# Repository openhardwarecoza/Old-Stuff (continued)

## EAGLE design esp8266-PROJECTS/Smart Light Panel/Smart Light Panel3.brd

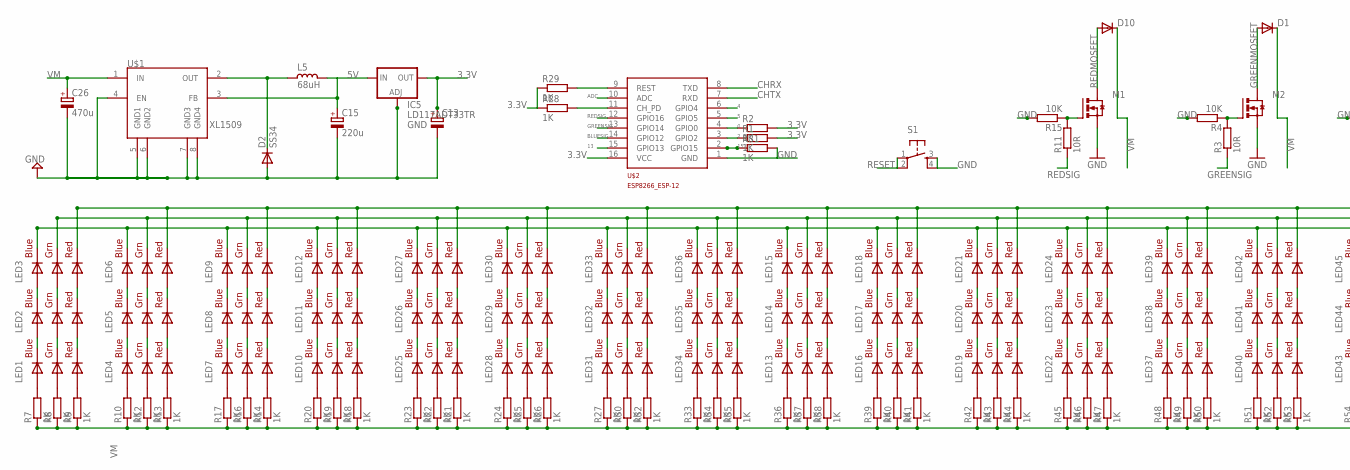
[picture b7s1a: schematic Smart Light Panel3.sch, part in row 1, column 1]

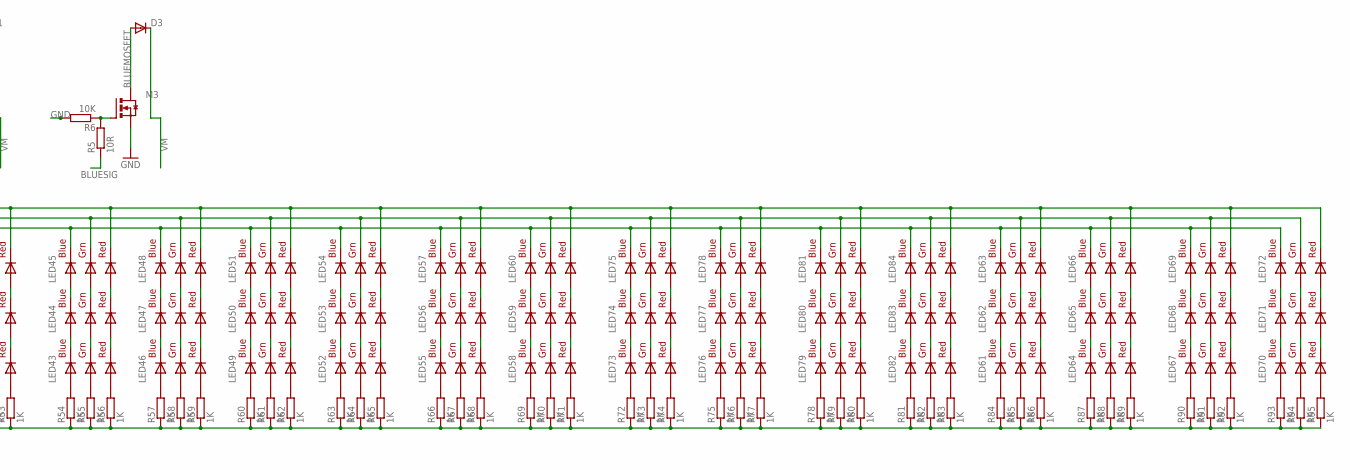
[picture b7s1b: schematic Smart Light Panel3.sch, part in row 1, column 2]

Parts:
C13: CPOL-EUE2.5-7; E2,5-7
C15: 220u; E2,5-7
C26: 470u; E2,5-7
D1, D3, D10: DIODESMA-ALT; SMA-DIODE_ALT
D2: SS34; DO-214AC
IC5: LD117ADT33TR; DPACK
L5: 68uH; CD75
LED1, LED2, LED3, LED4, LED5, LED6, LED7, LED8, LED9, LED10, LED11, LED12, LED13, LED14, LED15, LED16, LED17, LED18, LED19, LED20, LED21, LED22, LED23, LED24, LED25, LED26, LED27, LED28, LED29, LED30, LED31, LED32, LED33, LED34, LED35, LED36, LED37, LED38, LED39, LED40, LED41, LED42, LED43, LED44, LED45, LED46, LED47, LED48, LED49, LED50, LED51, LED52, LED53, LED54, LED55, LED56, LED57, LED58, LED59, LED60, LED61, LED62, LED63, LED64, LED65, LED66, LED67, LED68, LED69, LED70, LED71, LED72, LED73, LED74, LED75, LED76, LED77, LED78, LED79, LED80, LED81, LED82, LED83, LED84: RGBLED5050
M1, M2, M3: IRLR024N; TO252
R1, R2, R28, R29, R31: 1K; M1206
R3, R5, R11: 10R; M1206
R4, R6, R15: 10K; M1206
R7, R8, R9, R10, R12, R13, R14, R16, R17, R18, R19, R20, R21, R22, R23, R24, R25, R26, R27, R30, R32, R33, R34, R35, R36, R37, R38, R39, R40, R41, R42, R43, R44, R45, R46, R47, R48, R49, R50, R51, R52, R53, R54, R55, R56, R57, R58, R59, R60, R61, R62, R63, R64, R65, R66, R67, R68, R69, R70, R71, R72, R73, R74, R75, R76, R77, R78, R79, R80, R81, R82, R83, R84, R85, R86, R87, R88, R89, R90, R91, R92, R93, R94, R95: 1K; R0603
S1: TAC_SWITCHPTH; TACTILE-PTH
U$1: XL1509; SO08
U$2: ESP8266_ESP-12; ESP8266-ESP12

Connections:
0: R2.1, U$2.4 (GPIO0)
2: R1.1, U$2.3 (GPIO2)
3.3V: C13.+, IC5.4 (OUT), R1.2, R2.2, R28.1, R29.1, U$2.16 (VCC)
4: U$2.6 (GPIO4)
5: U$2.5 (GPIO5)
5V: C15.+, IC5.3 (IN), L5.1, U$1.3 (FB)
13: U$2.15 (GPIO13)
15: R31.1, U$2.2 (GPIO15)
ADC: U$2.10 (ADC)
BLUEMOSFET: D3.A, LED3.4 (BLUE_C), LED6.4 (BLUE_C), LED9.4 (BLUE_C), LED12.4 (BLUE_C), LED15.4 (BLUE_C), LED18.4 (BLUE_C), LED21.4 (BLUE_C), LED24.4 (BLUE_C), LED27.4 (BLUE_C), LED30.4 (BLUE_C), LED33.4 (BLUE_C), LED36.4 (BLUE_C), LED39.4 (BLUE_C), LED42.4 (BLUE_C), LED45.4 (BLUE_C), LED48.4 (BLUE_C), LED51.4 (BLUE_C), LED54.4 (BLUE_C), LED57.4 (BLUE_C), LED60.4 (BLUE_C), LED63.4 (BLUE_C), LED66.4 (BLUE_C), LED69.4 (BLUE_C), LED72.4 (BLUE_C), LED75.4 (BLUE_C), LED78.4 (BLUE_C), LED81.4 (BLUE_C), LED84.4 (BLUE_C), M3.3 (D)
BLUESIG: R5.1, U$2.14 (GPIO12)
CHRX: U$2.8 (TXD)
CHTX: U$2.7 (RXD)
GND: C13.-, C15.-, C26.-, D2.2 (A), IC5.1 (ADJ), M1.2 (S), M2.2 (S), M3.2 (S), R4.2, R6.2, R15.2, R31.2, S1.3, S1.4, U$1.4 (EN), U$1.5 (GND1), U$1.6 (GND2), U$1.7 (GND3), U$1.8 (GND4), U$2.1 (GND)
GREENMOSFET: D1.A, LED3.6 (GREEN_C), LED6.6 (GREEN_C), LED9.6 (GREEN_C), LED12.6 (GREEN_C), LED15.6 (GREEN_C), LED18.6 (GREEN_C), LED21.6 (GREEN_C), LED24.6 (GREEN_C), LED27.6 (GREEN_C), LED30.6 (GREEN_C), LED33.6 (GREEN_C), LED36.6 (GREEN_C), LED39.6 (GREEN_C), LED42.6 (GREEN_C), LED45.6 (GREEN_C), LED48.6 (GREEN_C), LED51.6 (GREEN_C), LED54.6 (GREEN_C), LED57.6 (GREEN_C), LED60.6 (GREEN_C), LED63.6 (GREEN_C), LED66.6 (GREEN_C), LED69.6 (GREEN_C), LED72.6 (GREEN_C), LED75.6 (GREEN_C), LED78.6 (GREEN_C), LED81.6 (GREEN_C), LED84.6 (GREEN_C), M2.3 (D)
GREENSIG: R3.1, U$2.13 (GPIO14)
unnamed: M2.1 (G), R3.2, R4.1
unnamed: LED2.4 (BLUE_C), LED3.3 (BLUE_A)
unnamed: LED2.6 (GREEN_C), LED3.1 (GREEN_A)
unnamed: M3.1 (G), R5.2, R6.1
unnamed: LED59.4 (BLUE_C), LED60.3 (BLUE_A)
unnamed: LED2.5 (RED_C), LED3.2 (RED_A)
unnamed: LED1.5 (RED_C), LED2.2 (RED_A)
unnamed: LED59.6 (GREEN_C), LED60.1 (GREEN_A)
unnamed: LED59.5 (RED_C), LED60.2 (RED_A)
unnamed: LED1.6 (GREEN_C), LED2.1 (GREEN_A)
unnamed: LED1.4 (BLUE_C), LED2.3 (BLUE_A)
unnamed: LED4.4 (BLUE_C), LED5.3 (BLUE_A)
unnamed: LED4.6 (GREEN_C), LED5.1 (GREEN_A)
unnamed: LED5.4 (BLUE_C), LED6.3 (BLUE_A)
unnamed: R28.2, U$2.11 (CH_PD)
unnamed: LED5.6 (GREEN_C), LED6.1 (GREEN_A)
unnamed: LED4.5 (RED_C), LED5.2 (RED_A)
unnamed: LED5.5 (RED_C), LED6.2 (RED_A)
unnamed: LED7.4 (BLUE_C), LED8.3 (BLUE_A)
unnamed: LED8.4 (BLUE_C), LED9.3 (BLUE_A)
unnamed: LED7.6 (GREEN_C), LED8.1 (GREEN_A)
unnamed: LED8.6 (GREEN_C), LED9.1 (GREEN_A)
unnamed: LED7.5 (RED_C), LED8.2 (RED_A)
unnamed: LED8.5 (RED_C), LED9.2 (RED_A)
unnamed: LED10.4 (BLUE_C), LED11.3 (BLUE_A)
unnamed: LED11.4 (BLUE_C), LED12.3 (BLUE_A)
unnamed: LED10.6 (GREEN_C), LED11.1 (GREEN_A)
unnamed: LED11.6 (GREEN_C), LED12.1 (GREEN_A)
unnamed: LED10.5 (RED_C), LED11.2 (RED_A)
unnamed: LED11.5 (RED_C), LED12.2 (RED_A)
unnamed: LED25.4 (BLUE_C), LED26.3 (BLUE_A)
unnamed: LED26.4 (BLUE_C), LED27.3 (BLUE_A)
unnamed: LED25.6 (GREEN_C), LED26.1 (GREEN_A)
unnamed: LED26.6 (GREEN_C), LED27.1 (GREEN_A)
unnamed: LED25.5 (RED_C), LED26.2 (RED_A)
unnamed: LED26.5 (RED_C), LED27.2 (RED_A)
unnamed: LED28.4 (BLUE_C), LED29.3 (BLUE_A)
unnamed: LED28.6 (GREEN_C), LED29.1 (GREEN_A)
unnamed: LED29.4 (BLUE_C), LED30.3 (BLUE_A)
unnamed: LED29.6 (GREEN_C), LED30.1 (GREEN_A)
unnamed: LED28.5 (RED_C), LED29.2 (RED_A)
unnamed: LED29.5 (RED_C), LED30.2 (RED_A)
unnamed: LED31.4 (BLUE_C), LED32.3 (BLUE_A)
unnamed: LED32.4 (BLUE_C), LED33.3 (BLUE_A)
unnamed: LED31.6 (GREEN_C), LED32.1 (GREEN_A)
unnamed: LED32.6 (GREEN_C), LED33.1 (GREEN_A)
unnamed: LED31.5 (RED_C), LED32.2 (RED_A)
unnamed: LED32.5 (RED_C), LED33.2 (RED_A)
unnamed: LED34.4 (BLUE_C), LED35.3 (BLUE_A)
unnamed: LED35.4 (BLUE_C), LED36.3 (BLUE_A)
unnamed: LED34.6 (GREEN_C), LED35.1 (GREEN_A)
unnamed: LED35.6 (GREEN_C), LED36.1 (GREEN_A)
unnamed: LED34.5 (RED_C), LED35.2 (RED_A)
unnamed: LED35.5 (RED_C), LED36.2 (RED_A)
unnamed: LED13.4 (BLUE_C), LED14.3 (BLUE_A)
unnamed: LED13.6 (GREEN_C), LED14.1 (GREEN_A)
unnamed: LED13.5 (RED_C), LED14.2 (RED_A)
unnamed: LED14.5 (RED_C), LED15.2 (RED_A)
unnamed: LED14.6 (GREEN_C), LED15.1 (GREEN_A)
unnamed: LED14.4 (BLUE_C), LED15.3 (BLUE_A)
unnamed: LED16.4 (BLUE_C), LED17.3 (BLUE_A)
unnamed: LED16.6 (GREEN_C), LED17.1 (GREEN_A)
unnamed: LED16.5 (RED_C), LED17.2 (RED_A)
unnamed: M1.1 (G), R11.2, R15.1
unnamed: LED17.5 (RED_C), LED18.2 (RED_A)
unnamed: LED17.6 (GREEN_C), LED18.1 (GREEN_A)
unnamed: LED17.4 (BLUE_C), LED18.3 (BLUE_A)
unnamed: LED19.4 (BLUE_C), LED20.3 (BLUE_A)
unnamed: LED19.6 (GREEN_C), LED20.1 (GREEN_A)
unnamed: LED19.5 (RED_C), LED20.2 (RED_A)
unnamed: LED20.5 (RED_C), LED21.2 (RED_A)
unnamed: LED20.6 (GREEN_C), LED21.1 (GREEN_A)
unnamed: LED20.4 (BLUE_C), LED21.3 (BLUE_A)
unnamed: LED22.4 (BLUE_C), LED23.3 (BLUE_A)
unnamed: LED22.6 (GREEN_C), LED23.1 (GREEN_A)
unnamed: LED22.5 (RED_C), LED23.2 (RED_A)
unnamed: LED23.5 (RED_C), LED24.2 (RED_A)
unnamed: LED23.6 (GREEN_C), LED24.1 (GREEN_A)
unnamed: LED23.4 (BLUE_C), LED24.3 (BLUE_A)
unnamed: LED37.4 (BLUE_C), LED38.3 (BLUE_A)
unnamed: LED37.6 (GREEN_C), LED38.1 (GREEN_A)
unnamed: LED37.5 (RED_C), LED38.2 (RED_A)
unnamed: LED38.5 (RED_C), LED39.2 (RED_A)
unnamed: LED38.6 (GREEN_C), LED39.1 (GREEN_A)
unnamed: LED38.4 (BLUE_C), LED39.3 (BLUE_A)
unnamed: LED40.5 (RED_C), LED41.2 (RED_A)
unnamed: LED40.6 (GREEN_C), LED41.1 (GREEN_A)
unnamed: LED40.4 (BLUE_C), LED41.3 (BLUE_A)
unnamed: D2.1 (C), L5.2, U$1.2 (OUT)
unnamed: LED41.4 (BLUE_C), LED42.3 (BLUE_A)
unnamed: LED41.6 (GREEN_C), LED42.1 (GREEN_A)
unnamed: LED41.5 (RED_C), LED42.2 (RED_A)
unnamed: LED43.4 (BLUE_C), LED44.3 (BLUE_A)
unnamed: LED43.6 (GREEN_C), LED44.1 (GREEN_A)
unnamed: LED43.5 (RED_C), LED44.2 (RED_A)
unnamed: LED44.5 (RED_C), LED45.2 (RED_A)
unnamed: LED44.6 (GREEN_C), LED45.1 (GREEN_A)
unnamed: LED44.4 (BLUE_C), LED45.3 (BLUE_A)
unnamed: LED46.4 (BLUE_C), LED47.3 (BLUE_A)
unnamed: LED46.6 (GREEN_C), LED47.1 (GREEN_A)
unnamed: LED46.5 (RED_C), LED47.2 (RED_A)
unnamed: LED47.5 (RED_C), LED48.2 (RED_A)
unnamed: LED47.6 (GREEN_C), LED48.1 (GREEN_A)
unnamed: LED47.4 (BLUE_C), LED48.3 (BLUE_A)
unnamed: LED50.5 (RED_C), LED51.2 (RED_A)
unnamed: LED50.6 (GREEN_C), LED51.1 (GREEN_A)
unnamed: LED50.4 (BLUE_C), LED51.3 (BLUE_A)
unnamed: LED49.4 (BLUE_C), LED50.3 (BLUE_A)
unnamed: LED49.6 (GREEN_C), LED50.1 (GREEN_A)
unnamed: LED49.5 (RED_C), LED50.2 (RED_A)
unnamed: LED52.4 (BLUE_C), LED53.3 (BLUE_A)
unnamed: LED52.6 (GREEN_C), LED53.1 (GREEN_A)
unnamed: LED52.5 (RED_C), LED53.2 (RED_A)
unnamed: LED53.5 (RED_C), LED54.2 (RED_A)
unnamed: LED53.6 (GREEN_C), LED54.1 (GREEN_A)
unnamed: LED53.4 (BLUE_C), LED54.3 (BLUE_A)
unnamed: LED56.5 (RED_C), LED57.2 (RED_A)
unnamed: LED56.6 (GREEN_C), LED57.1 (GREEN_A)
unnamed: LED56.4 (BLUE_C), LED57.3 (BLUE_A)
unnamed: LED55.4 (BLUE_C), LED56.3 (BLUE_A)
unnamed: LED55.6 (GREEN_C), LED56.1 (GREEN_A)
unnamed: LED55.5 (RED_C), LED56.2 (RED_A)
unnamed: LED58.4 (BLUE_C), LED59.3 (BLUE_A)
unnamed: LED58.6 (GREEN_C), LED59.1 (GREEN_A)
unnamed: LED58.5 (RED_C), LED59.2 (RED_A)
unnamed: LED73.4 (BLUE_C), LED74.3 (BLUE_A)
unnamed: LED73.6 (GREEN_C), LED74.1 (GREEN_A)
unnamed: LED73.5 (RED_C), LED74.2 (RED_A)
unnamed: LED74.5 (RED_C), LED75.2 (RED_A)
unnamed: LED74.6 (GREEN_C), LED75.1 (GREEN_A)
unnamed: LED74.4 (BLUE_C), LED75.3 (BLUE_A)
unnamed: LED76.4 (BLUE_C), LED77.3 (BLUE_A)
unnamed: LED77.4 (BLUE_C), LED78.3 (BLUE_A)
unnamed: LED77.6 (GREEN_C), LED78.1 (GREEN_A)
unnamed: LED76.6 (GREEN_C), LED77.1 (GREEN_A)
unnamed: LED76.5 (RED_C), LED77.2 (RED_A)
unnamed: LED77.5 (RED_C), LED78.2 (RED_A)
unnamed: LED80.4 (BLUE_C), LED81.3 (BLUE_A)
unnamed: LED80.6 (GREEN_C), LED81.1 (GREEN_A)
unnamed: LED80.5 (RED_C), LED81.2 (RED_A)
unnamed: LED79.5 (RED_C), LED80.2 (RED_A)
unnamed: LED79.6 (GREEN_C), LED80.1 (GREEN_A)
unnamed: LED79.4 (BLUE_C), LED80.3 (BLUE_A)
unnamed: LED82.4 (BLUE_C), LED83.3 (BLUE_A)
unnamed: LED83.4 (BLUE_C), LED84.3 (BLUE_A)
unnamed: LED83.6 (GREEN_C), LED84.1 (GREEN_A)
unnamed: LED82.6 (GREEN_C), LED83.1 (GREEN_A)
unnamed: LED82.5 (RED_C), LED83.2 (RED_A)
unnamed: LED83.5 (RED_C), LED84.2 (RED_A)
unnamed: LED62.4 (BLUE_C), LED63.3 (BLUE_A)
unnamed: LED61.4 (BLUE_C), LED62.3 (BLUE_A)
unnamed: LED61.6 (GREEN_C), LED62.1 (GREEN_A)
unnamed: LED62.6 (GREEN_C), LED63.1 (GREEN_A)
unnamed: LED62.5 (RED_C), LED63.2 (RED_A)
unnamed: LED61.5 (RED_C), LED62.2 (RED_A)
unnamed: LED65.4 (BLUE_C), LED66.3 (BLUE_A)
unnamed: LED64.4 (BLUE_C), LED65.3 (BLUE_A)
unnamed: LED65.6 (GREEN_C), LED66.1 (GREEN_A)
unnamed: LED64.6 (GREEN_C), LED65.1 (GREEN_A)
unnamed: LED64.5 (RED_C), LED65.2 (RED_A)
unnamed: LED65.5 (RED_C), LED66.2 (RED_A)
unnamed: LED67.4 (BLUE_C), LED68.3 (BLUE_A)
unnamed: LED68.4 (BLUE_C), LED69.3 (BLUE_A)
unnamed: LED68.6 (GREEN_C), LED69.1 (GREEN_A)
unnamed: LED67.6 (GREEN_C), LED68.1 (GREEN_A)
unnamed: LED67.5 (RED_C), LED68.2 (RED_A)
unnamed: LED68.5 (RED_C), LED69.2 (RED_A)
unnamed: LED71.4 (BLUE_C), LED72.3 (BLUE_A)
unnamed: LED70.4 (BLUE_C), LED71.3 (BLUE_A)
unnamed: LED70.6 (GREEN_C), LED71.1 (GREEN_A)
unnamed: LED70.5 (RED_C), LED71.2 (RED_A)
unnamed: LED71.5 (RED_C), LED72.2 (RED_A)
unnamed: LED71.6 (GREEN_C), LED72.1 (GREEN_A)
unnamed: LED1.3 (BLUE_A), R7.2
unnamed: LED1.1 (GREEN_A), R8.2
unnamed: LED1.2 (RED_A), R9.2
unnamed: LED4.3 (BLUE_A), R10.2
unnamed: LED4.1 (GREEN_A), R12.2
unnamed: LED4.2 (RED_A), R13.2
unnamed: LED7.2 (RED_A), R14.2
unnamed: LED7.1 (GREEN_A), R16.2
unnamed: LED7.3 (BLUE_A), R17.2
unnamed: LED10.2 (RED_A), R18.2
unnamed: LED10.1 (GREEN_A), R19.2
unnamed: LED10.3 (BLUE_A), R20.2
unnamed: LED25.2 (RED_A), R21.2
unnamed: LED25.1 (GREEN_A), R22.2
unnamed: LED25.3 (BLUE_A), R23.2
unnamed: LED28.3 (BLUE_A), R24.2
unnamed: LED28.1 (GREEN_A), R25.2
unnamed: LED28.2 (RED_A), R26.2
unnamed: LED31.3 (BLUE_A), R27.2
unnamed: LED31.1 (GREEN_A), R30.2
unnamed: LED31.2 (RED_A), R32.2
unnamed: LED34.3 (BLUE_A), R33.2
unnamed: LED34.1 (GREEN_A), R34.2
unnamed: LED34.2 (RED_A), R35.2
unnamed: LED13.3 (BLUE_A), R36.2
unnamed: LED13.1 (GREEN_A), R37.2
unnamed: LED13.2 (RED_A), R38.2
unnamed: LED16.3 (BLUE_A), R39.2
unnamed: LED16.1 (GREEN_A), R40.2
unnamed: LED16.2 (RED_A), R41.2
unnamed: LED19.3 (BLUE_A), R42.2
unnamed: LED19.1 (GREEN_A), R43.2
unnamed: LED19.2 (RED_A), R44.2
unnamed: LED22.3 (BLUE_A), R45.2
unnamed: LED22.1 (GREEN_A), R46.2
unnamed: LED22.2 (RED_A), R47.2
unnamed: LED37.3 (BLUE_A), R48.2
unnamed: LED37.1 (GREEN_A), R49.2
unnamed: LED37.2 (RED_A), R50.2
unnamed: LED40.3 (BLUE_A), R51.2
unnamed: LED40.1 (GREEN_A), R52.2
unnamed: LED40.2 (RED_A), R53.2
unnamed: LED43.3 (BLUE_A), R54.2
unnamed: LED43.1 (GREEN_A), R55.2
unnamed: LED43.2 (RED_A), R56.2
unnamed: LED46.3 (BLUE_A), R57.2
unnamed: LED46.1 (GREEN_A), R58.2
unnamed: LED46.2 (RED_A), R59.2
unnamed: LED49.3 (BLUE_A), R60.2
unnamed: LED49.1 (GREEN_A), R61.2
unnamed: LED49.2 (RED_A), R62.2
unnamed: LED52.3 (BLUE_A), R63.2
unnamed: LED52.1 (GREEN_A), R64.2
unnamed: LED52.2 (RED_A), R65.2
unnamed: LED55.3 (BLUE_A), R66.2
unnamed: LED55.1 (GREEN_A), R67.2
unnamed: LED55.2 (RED_A), R68.2
unnamed: LED58.3 (BLUE_A), R69.2
unnamed: LED58.1 (GREEN_A), R70.2
unnamed: LED58.2 (RED_A), R71.2
unnamed: LED73.3 (BLUE_A), R72.2
unnamed: LED73.1 (GREEN_A), R73.2
unnamed: LED73.2 (RED_A), R74.2
unnamed: LED76.3 (BLUE_A), R75.2
unnamed: LED76.1 (GREEN_A), R76.2
unnamed: LED76.2 (RED_A), R77.2
unnamed: LED79.3 (BLUE_A), R78.2
unnamed: LED79.1 (GREEN_A), R79.2
unnamed: LED79.2 (RED_A), R80.2
unnamed: LED82.3 (BLUE_A), R81.2
unnamed: LED82.1 (GREEN_A), R82.2
unnamed: LED82.2 (RED_A), R83.2
unnamed: LED61.3 (BLUE_A), R84.2
unnamed: LED61.1 (GREEN_A), R85.2
unnamed: LED61.2 (RED_A), R86.2
unnamed: LED64.3 (BLUE_A), R87.2
unnamed: LED64.1 (GREEN_A), R88.2
unnamed: LED64.2 (RED_A), R89.2
unnamed: LED67.3 (BLUE_A), R90.2
unnamed: LED67.1 (GREEN_A), R91.2
unnamed: LED67.2 (RED_A), R92.2
unnamed: LED70.3 (BLUE_A), R93.2
unnamed: LED70.1 (GREEN_A), R94.2
unnamed: LED70.2 (RED_A), R95.2
REDMOSFET: D10.A, LED3.5 (RED_C), LED6.5 (RED_C), LED9.5 (RED_C), LED12.5 (RED_C), LED15.5 (RED_C), LED18.5 (RED_C), LED21.5 (RED_C), LED24.5 (RED_C), LED27.5 (RED_C), LED30.5 (RED_C), LED33.5 (RED_C), LED36.5 (RED_C), LED39.5 (RED_C), LED42.5 (RED_C), LED45.5 (RED_C), LED48.5 (RED_C), LED51.5 (RED_C), LED54.5 (RED_C), LED57.5 (RED_C), LED60.5 (RED_C), LED63.5 (RED_C), LED66.5 (RED_C), LED69.5 (RED_C), LED72.5 (RED_C), LED75.5 (RED_C), LED78.5 (RED_C), LED81.5 (RED_C), LED84.5 (RED_C), M1.3 (D)
REDSIG: R11.1, U$2.12 (GPIO16)
RESET: R29.2, S1.1, S1.2, U$2.9 (REST)
VM: C26.+, D1.C, D3.C, D10.C, R7.1, R8.1, R9.1, R10.1, R12.1, R13.1, R14.1, R16.1, R17.1, R18.1, R19.1, R20.1, R21.1, R22.1, R23.1, R24.1, R25.1, R26.1, R27.1, R30.1, R32.1, R33.1, R34.1, R35.1, R36.1, R37.1, R38.1, R39.1, R40.1, R41.1, R42.1, R43.1, R44.1, R45.1, R46.1, R47.1, R48.1, R49.1, R50.1, R51.1, R52.1, R53.1, R54.1, R55.1, R56.1, R57.1, R58.1, R59.1, R60.1, R61.1, R62.1, R63.1, R64.1, R65.1, R66.1, R67.1, R68.1, R69.1, R70.1, R71.1, R72.1, R73.1, R74.1, R75.1, R76.1, R77.1, R78.1, R79.1, R80.1, R81.1, R82.1, R83.1, R84.1, R85.1, R86.1, R87.1, R88.1, R89.1, R90.1, R91.1, R92.1, R93.1, R94.1, R95.1, U$1.1 (IN)

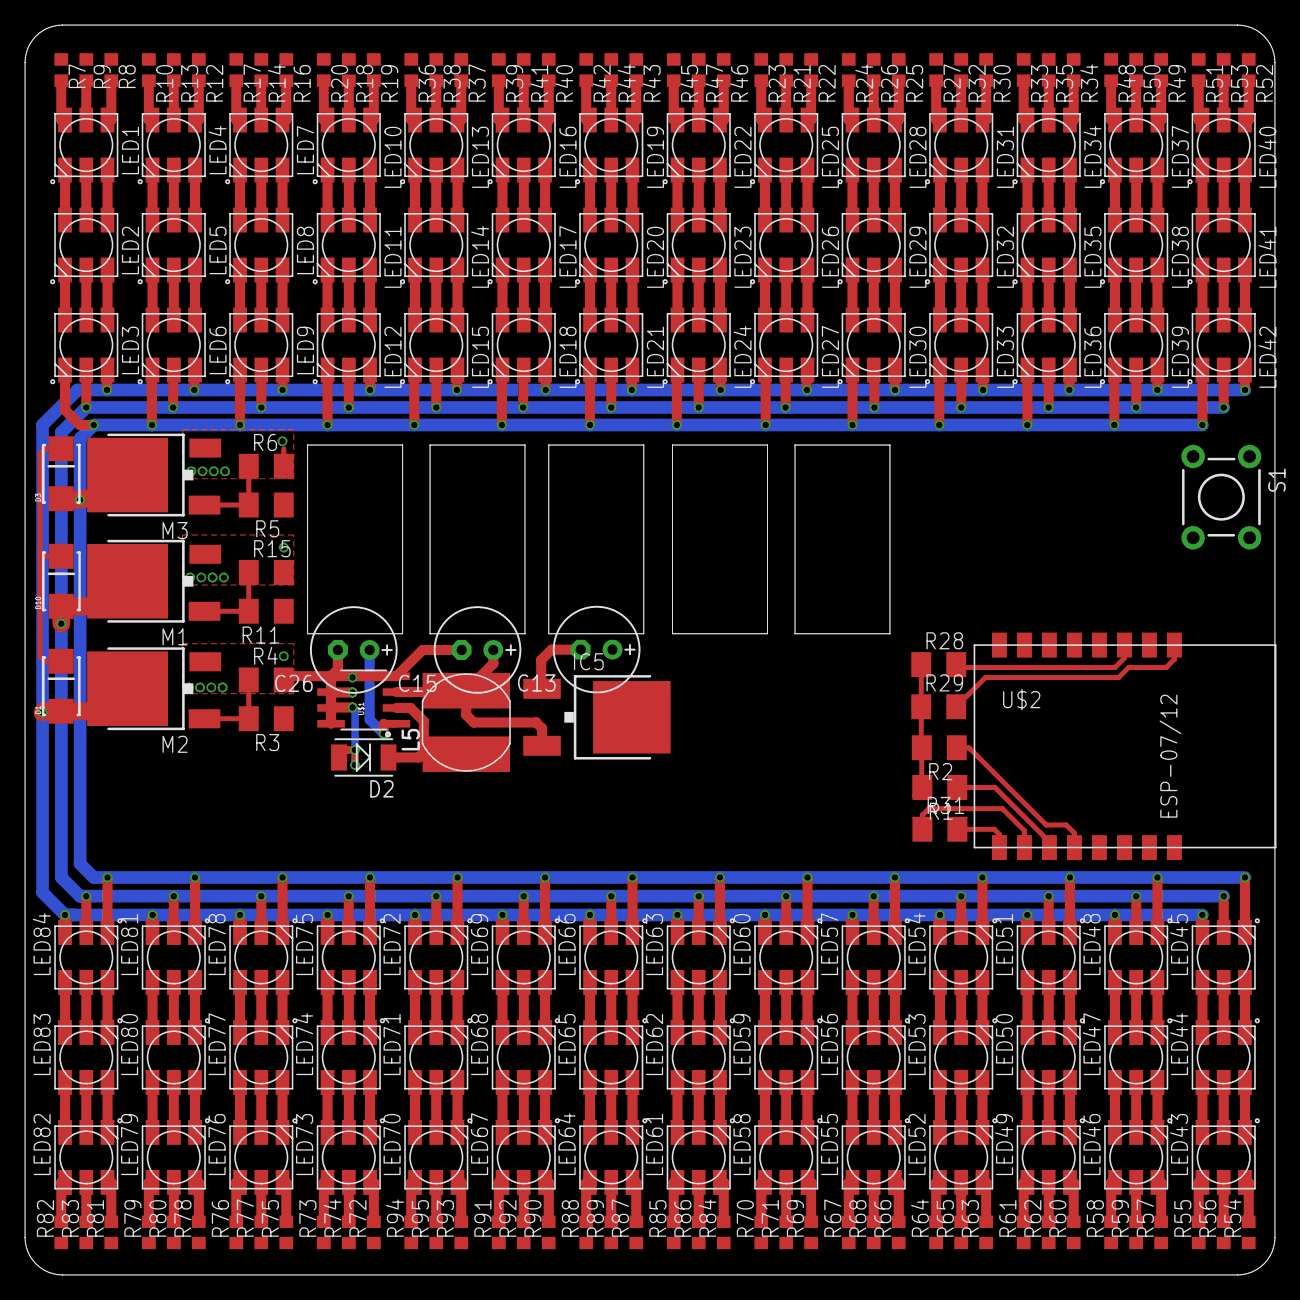
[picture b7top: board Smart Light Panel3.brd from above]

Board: 2 copper layers, 100.0 x 100.0 mm, 194 parts (0 on the bottom side), 271 nets.
